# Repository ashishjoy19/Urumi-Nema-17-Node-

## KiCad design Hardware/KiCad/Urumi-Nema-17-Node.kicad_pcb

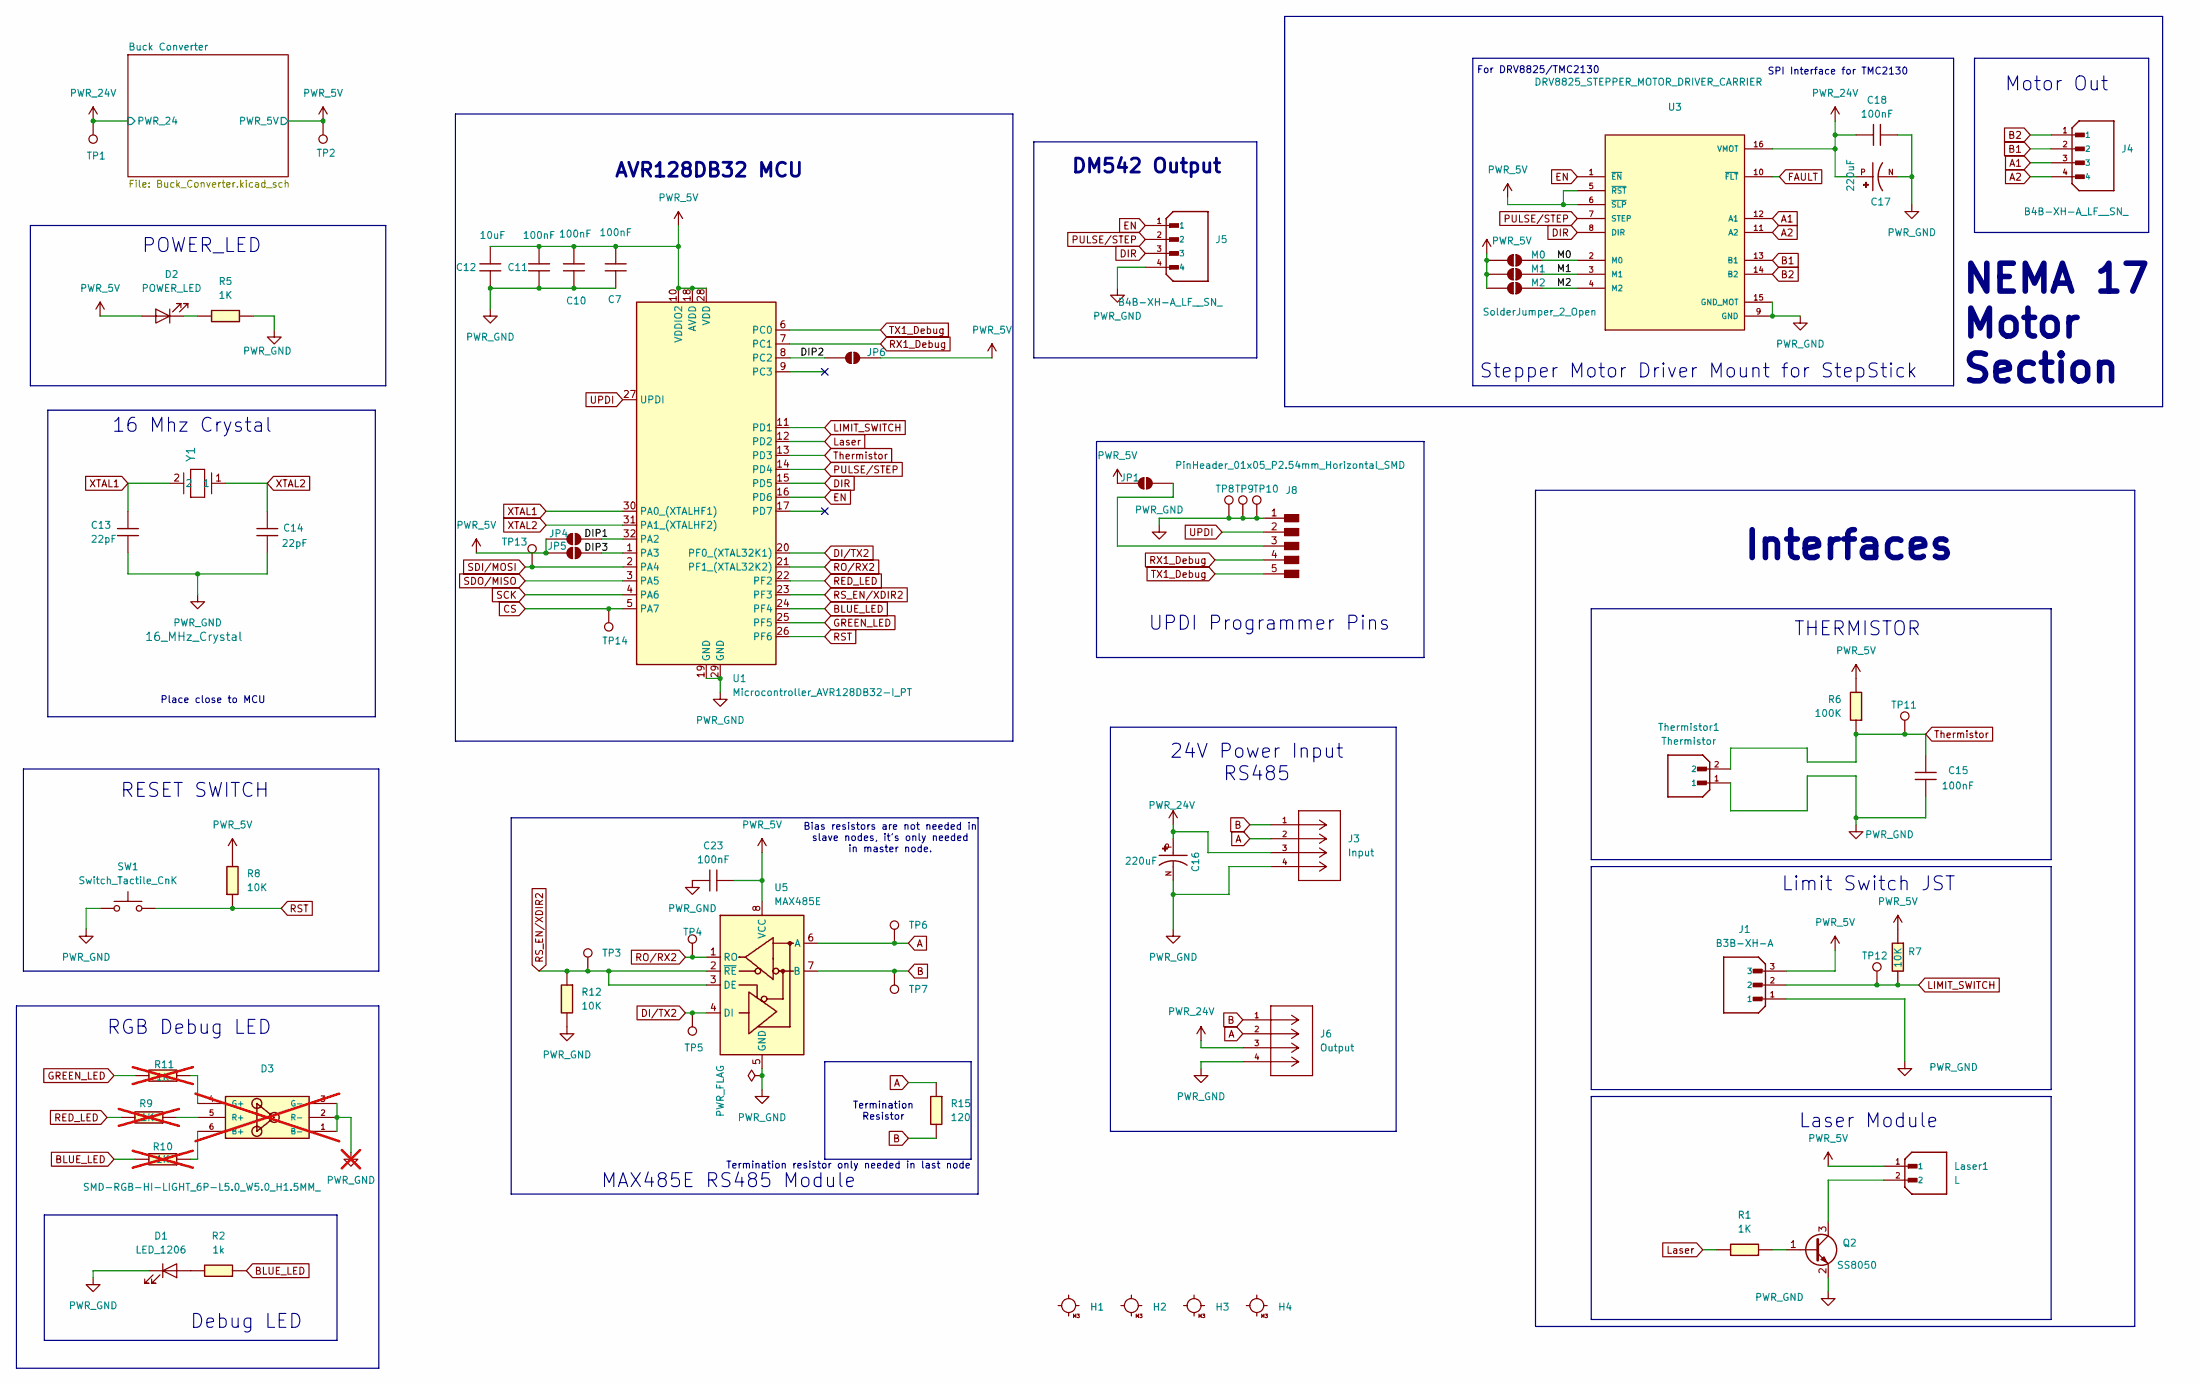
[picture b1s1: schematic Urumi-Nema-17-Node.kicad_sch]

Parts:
C7, C10, C11, C15, C18, C23: 100nF; C_0805_2012Metric_Pad1.18x1.45mm_HandSolder
C12: 10uF; C_1206
C13, C14: 22pF; C_0805_2012Metric_Pad1.18x1.45mm_HandSolder
C16, C17: 220uF; CAPPRD500W60D800H2000; PARTREV 28-FEB-20
D1: LED_1206
D2: POWER_LED; LED_1206
D3: SMD-RGB-HI-LIGHT_6P-L5.0_W5.0_H1.5MM_; LED6-SMD-5050; MPN 5050RGB; not fitted
H1, H2, H3, H4: MountingHole_M3
J1: B3B-XH-A; JST_B3B-XH-A; PARTREV 7/4/21
J3: Input; CONN_SD-39501-001_04P_MOL; MANUFACTURER_PART_NUMBER 395016004
J4, J5: B4B-XH-A_LF__SN_; JST_B4B-XH-A_LF__SN_; PARTREV 7/4/21
J6: Output; CONN_SD-39501-001_04P_MOL; MANUFACTURER_PART_NUMBER 395016004
J8: PinHeader_01x05_P2.54mm_Horizontal_SMD
JP1, JP4, JP5, JP6: SolderJumper_2_Open; SolderJumper-2_P1.3mm_Open_Pad1.0x1.5mm
Laser1: L; JST_B2B-XH-A_LF__SN_; PARTREV N/A
M0, M1, M2: SolderJumper_2_Open; SolderJumper-2_P1.3mm_Open_Pad1.0x1.5mm
Q2: SS8050; SOT-23
R1, R5: 1K; R_0805_2012Metric_Pad1.20x1.40mm_HandSolder
R2: 1k; R_0805_2012Metric_Pad1.20x1.40mm_HandSolder
R6: 100K; R_0805_2012Metric_Pad1.20x1.40mm_HandSolder
R7, R8, R12: 10K; R_0805_2012Metric_Pad1.20x1.40mm_HandSolder
R9, R10, R11: 1K; R_0805_2012Metric_Pad1.20x1.40mm_HandSolder; not fitted
R15: 120; R_0805_2012Metric_Pad1.20x1.40mm_HandSolder
SW1: Switch_Tactile_CnK; Button_Mini_3.9x3
TP1, TP2, TP3, TP4, TP5, TP6, TP7, TP8, TP9, TP10, TP11, TP12, TP13, TP14: TestPoint; TestPoint_Pad_1.0x1.0mm
Thermistor1: Thermistor; JST_B2B-XH-A_LF__SN_; PARTREV N/A
U1: Microcontroller_AVR128DB32-I_PT; TQFP-32_7x7mm_P0.8mm
U3: DRV8825_STEPPER_MOTOR_DRIVER_CARRIER; IC_DRV8825_STEPPER_MOTOR_DRIVER_CARRIER
U5: MAX485E; SOIC-8_3.9x4.9mm_P1.27mm
Y1: 16_MHz_Crystal; H32_RAM

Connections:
/DIP1: JP4.2 (B), U1.32 (PA2)
/DIP2: JP6.1 (A), U1.8 (PC2)
/DIP3: JP5.2 (B), U1.1 (PA3)
/M0: M0.2 (B), U3.2 (M0)
/M1: M1.2 (B), U3.3 (M1)
/M2: M2.2 (B), U3.4 (M2)
A: J3.2, J6.2, R15.2, TP6.1 (1_1), U5.6 (A)
A1: J4.3, U3.12 (A1)
A2: J4.4, U3.11 (A2)
B: J3.1, J6.1, R15.1, TP7.1 (1_1), U5.7 (B)
B1: J4.2, U3.13 (B1)
B2: J4.1, U3.14 (B2)
BLUE_LED: R2.2, R10.1, U1.24 (PF4)
CS: TP14.1 (1_1), U1.5 (PA7)
DIR: J5.3, U1.15 (PD5), U3.8 (DIR)
DI/TX2: TP5.1 (1_1), U1.20 (PF0_(XTAL32K1)), U5.4 (DI)
EN: J5.1, U1.16 (PD6), U3.1 (~EN)
FAULT: U3.10 (~FLT)
GREEN_LED: R11.1, U1.25 (PF5)
LIMIT_SWITCH: J1.2, R7.1, TP12.1 (1_1), U1.11 (PD1)
Laser: R1.1, U1.12 (PD2)
unnamed: D1.2 (A), R2.1
unnamed: D2.1 (K), R5.2
unnamed: D3.4 (G+), R11.2
unnamed: D3.5 (R+), R9.2
unnamed: D3.6 (B+), R10.2
unnamed: J8.3, JP1.2 (B)
unnamed: Q2.1 (B), R1.2
unnamed: Laser1.2, Q2.3 (C)
PULSE/STEP: J5.2, U1.14 (PD4), U3.7 (STEP)
PWR_5V: C7.1, C10.1, C11.1, C12.1, C23.2, D2.2 (A), J1.3, JP1.1 (A), JP4.1 (A), JP5.1 (A), JP6.2 (B), Laser1.1, M0.1 (A), M1.1 (A), M2.1 (A), R6.1, R7.2, R8.1, TP2.1 (1_1), U1.10 (VDDIO2), U1.18 (AVDD), U1.28 (VDD), U3.5 (~RST), U3.6 (~SLP), U5.8 (VCC); also elsewhere on the board
PWR_24V: C16.P, C17.P, C18.1, J3.3, J6.3, TP1.1 (1_1), U3.16 (VMOT); also elsewhere on the board
PWR_GND: C7.2, C10.2, C11.2, C12.2, C13.2, C14.2, C15.2, C16.N, C17.N, C18.2, C23.1, D1.1 (K), D3.1 (B-), D3.2 (R-), D3.3 (G-), J1.1, J3.4, J5.4, J6.4, J8.1, Q2.2 (E), R5.1, R12.1, SW1.1, TP8.1 (1_1), TP9.1 (1_1), TP10.1 (1_1), Thermistor1.1, U1.19 (GND), U1.29 (GND), U3.9 (GND), U3.15 (GND_MOT), U5.5 (GND); also elsewhere on the board
RED_LED: R9.1, U1.22 (PF2)
RO/RX2: TP4.1 (1_1), U1.21 (PF1_(XTAL32K2)), U5.1 (RO)
RST: R8.2, SW1.2, U1.26 (PF6)
RS_EN/XDIR2: R12.2, TP3.1 (1_1), U1.23 (PF3), U5.2 (~RE), U5.3 (DE)
RX1_Debug: J8.4, U1.7 (PC1)
SCK: U1.4 (PA6)
SDI/MOSI: TP13.1 (1_1), U1.2 (PA4)
SDO/MISO: U1.3 (PA5)
TX1_Debug: J8.5, U1.6 (PC0)
Thermistor: C15.1, R6.2, TP11.1 (1_1), Thermistor1.2, U1.13 (PD3)
UPDI: J8.2, U1.27 (UPDI)
XTAL1: C13.1, U1.30 (PA0_(XTALHF1)), Y1.2
XTAL2: C14.1, U1.31 (PA1_(XTALHF2)), Y1.1

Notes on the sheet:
RESET SWITCH
Bias resistors are not needed in slave nodes, it's only needed in master node.
MAX485E RS485 Module
THERMISTOR
16 Mhz Crystal
Termination Resistor
Laser Module
AVR128DB32 MCU
Limit Switch JST
SPI Interface for TMC2130
Interfaces
Debug LED
Termination resistor only needed in last node
RGB Debug LED
NEMA 17 Motor Section
DM542 Output
24V Power Input RS485
For DRV8825/TMC2130
Stepper Motor Driver Mount for StepStick
UPDI Programmer Pins
POWER_LED
Motor Out
Place close to MCU

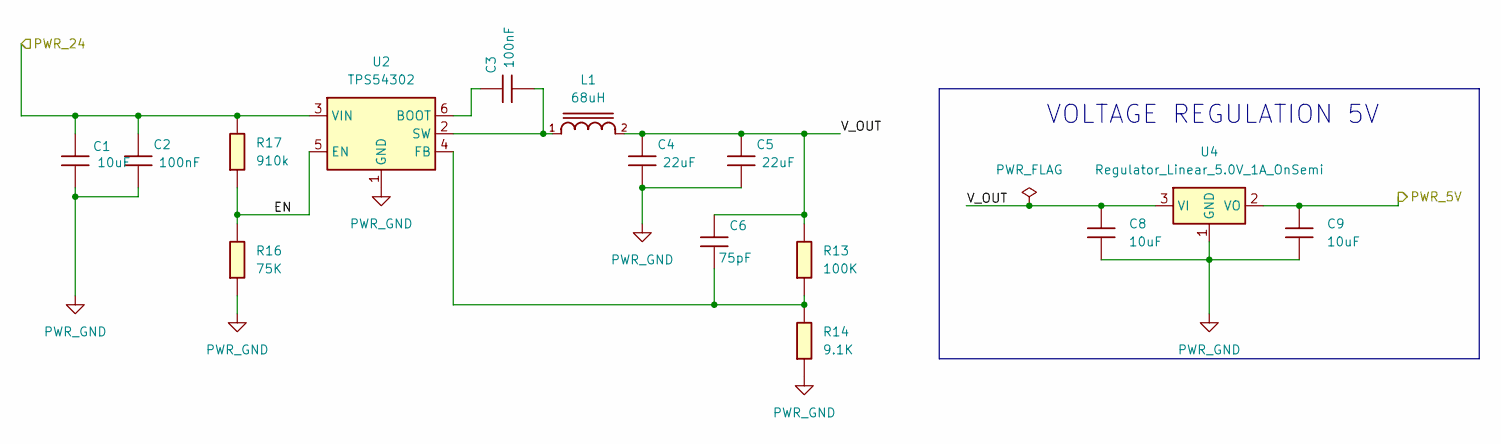
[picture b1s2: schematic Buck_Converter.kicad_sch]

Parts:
C1, C8, C9: 10uF; C_0805_2012Metric_Pad1.18x1.45mm_HandSolder
C2, C3: 100nF; C_0805_2012Metric_Pad1.18x1.45mm_HandSolder
C4, C5: 22uF; C_1206_3216Metric_Pad1.33x1.80mm_HandSolder
C6: 75pF; C_1206
L1: 68uH; CDRH104R
R13: 100K; R_0805_2012Metric_Pad1.20x1.40mm_HandSolder
R14: 9.1K; R_0805_2012Metric_Pad1.20x1.40mm_HandSolder
R16: 75K; R_0805_2012Metric_Pad1.20x1.40mm_HandSolder
R17: 910k; R_0805_2012Metric_Pad1.20x1.40mm_HandSolder
U2: TPS54302; SOT-23-6
U4: Regulator_Linear_5.0V_1A_OnSemi; SOT-223-3_TabPin2

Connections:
/Buck Converter/EN: R16.1, R17.2, U2.5 (EN)
/Buck Converter/V_OUT: C4.1, C5.1, C6.1, C8.1, L1.2, R13.1, U4.3 (VI)
unnamed: C3.1, U2.6 (BOOT)
unnamed: C6.2, R13.2, R14.1, U2.4 (FB)
unnamed: C3.2, L1.1, U2.2 (SW)
PWR_5V: C9.1, U4.2 (VO); also elsewhere on the board
PWR_24V: C1.1, C2.1, R17.1, U2.3 (VIN); also elsewhere on the board
PWR_GND: C1.2, C2.2, C4.2, C5.2, C8.2, C9.2, R14.2, R16.2, U2.1 (GND), U4.1 (GND); also elsewhere on the board

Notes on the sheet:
VOLTAGE REGULATION 5V

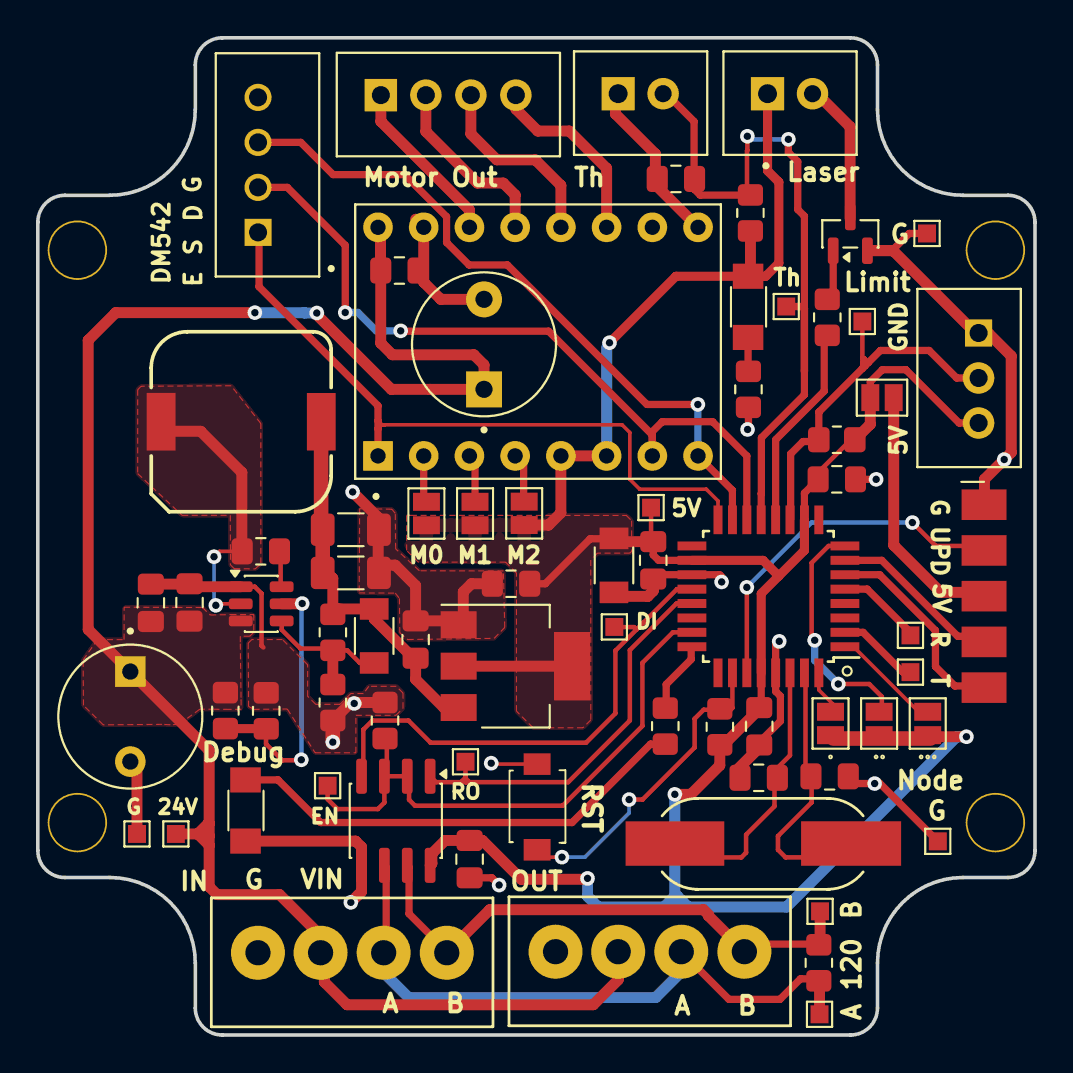
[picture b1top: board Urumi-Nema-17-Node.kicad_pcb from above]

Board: 2 copper layers, 55.4 x 55.4 mm, 75 parts (0 on the bottom side), 43 nets.

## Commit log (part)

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2026-06-22 Kicad Project created
2026-06-22 hw: Basic schematic setup
2026-06-23 hw: renamed folder
